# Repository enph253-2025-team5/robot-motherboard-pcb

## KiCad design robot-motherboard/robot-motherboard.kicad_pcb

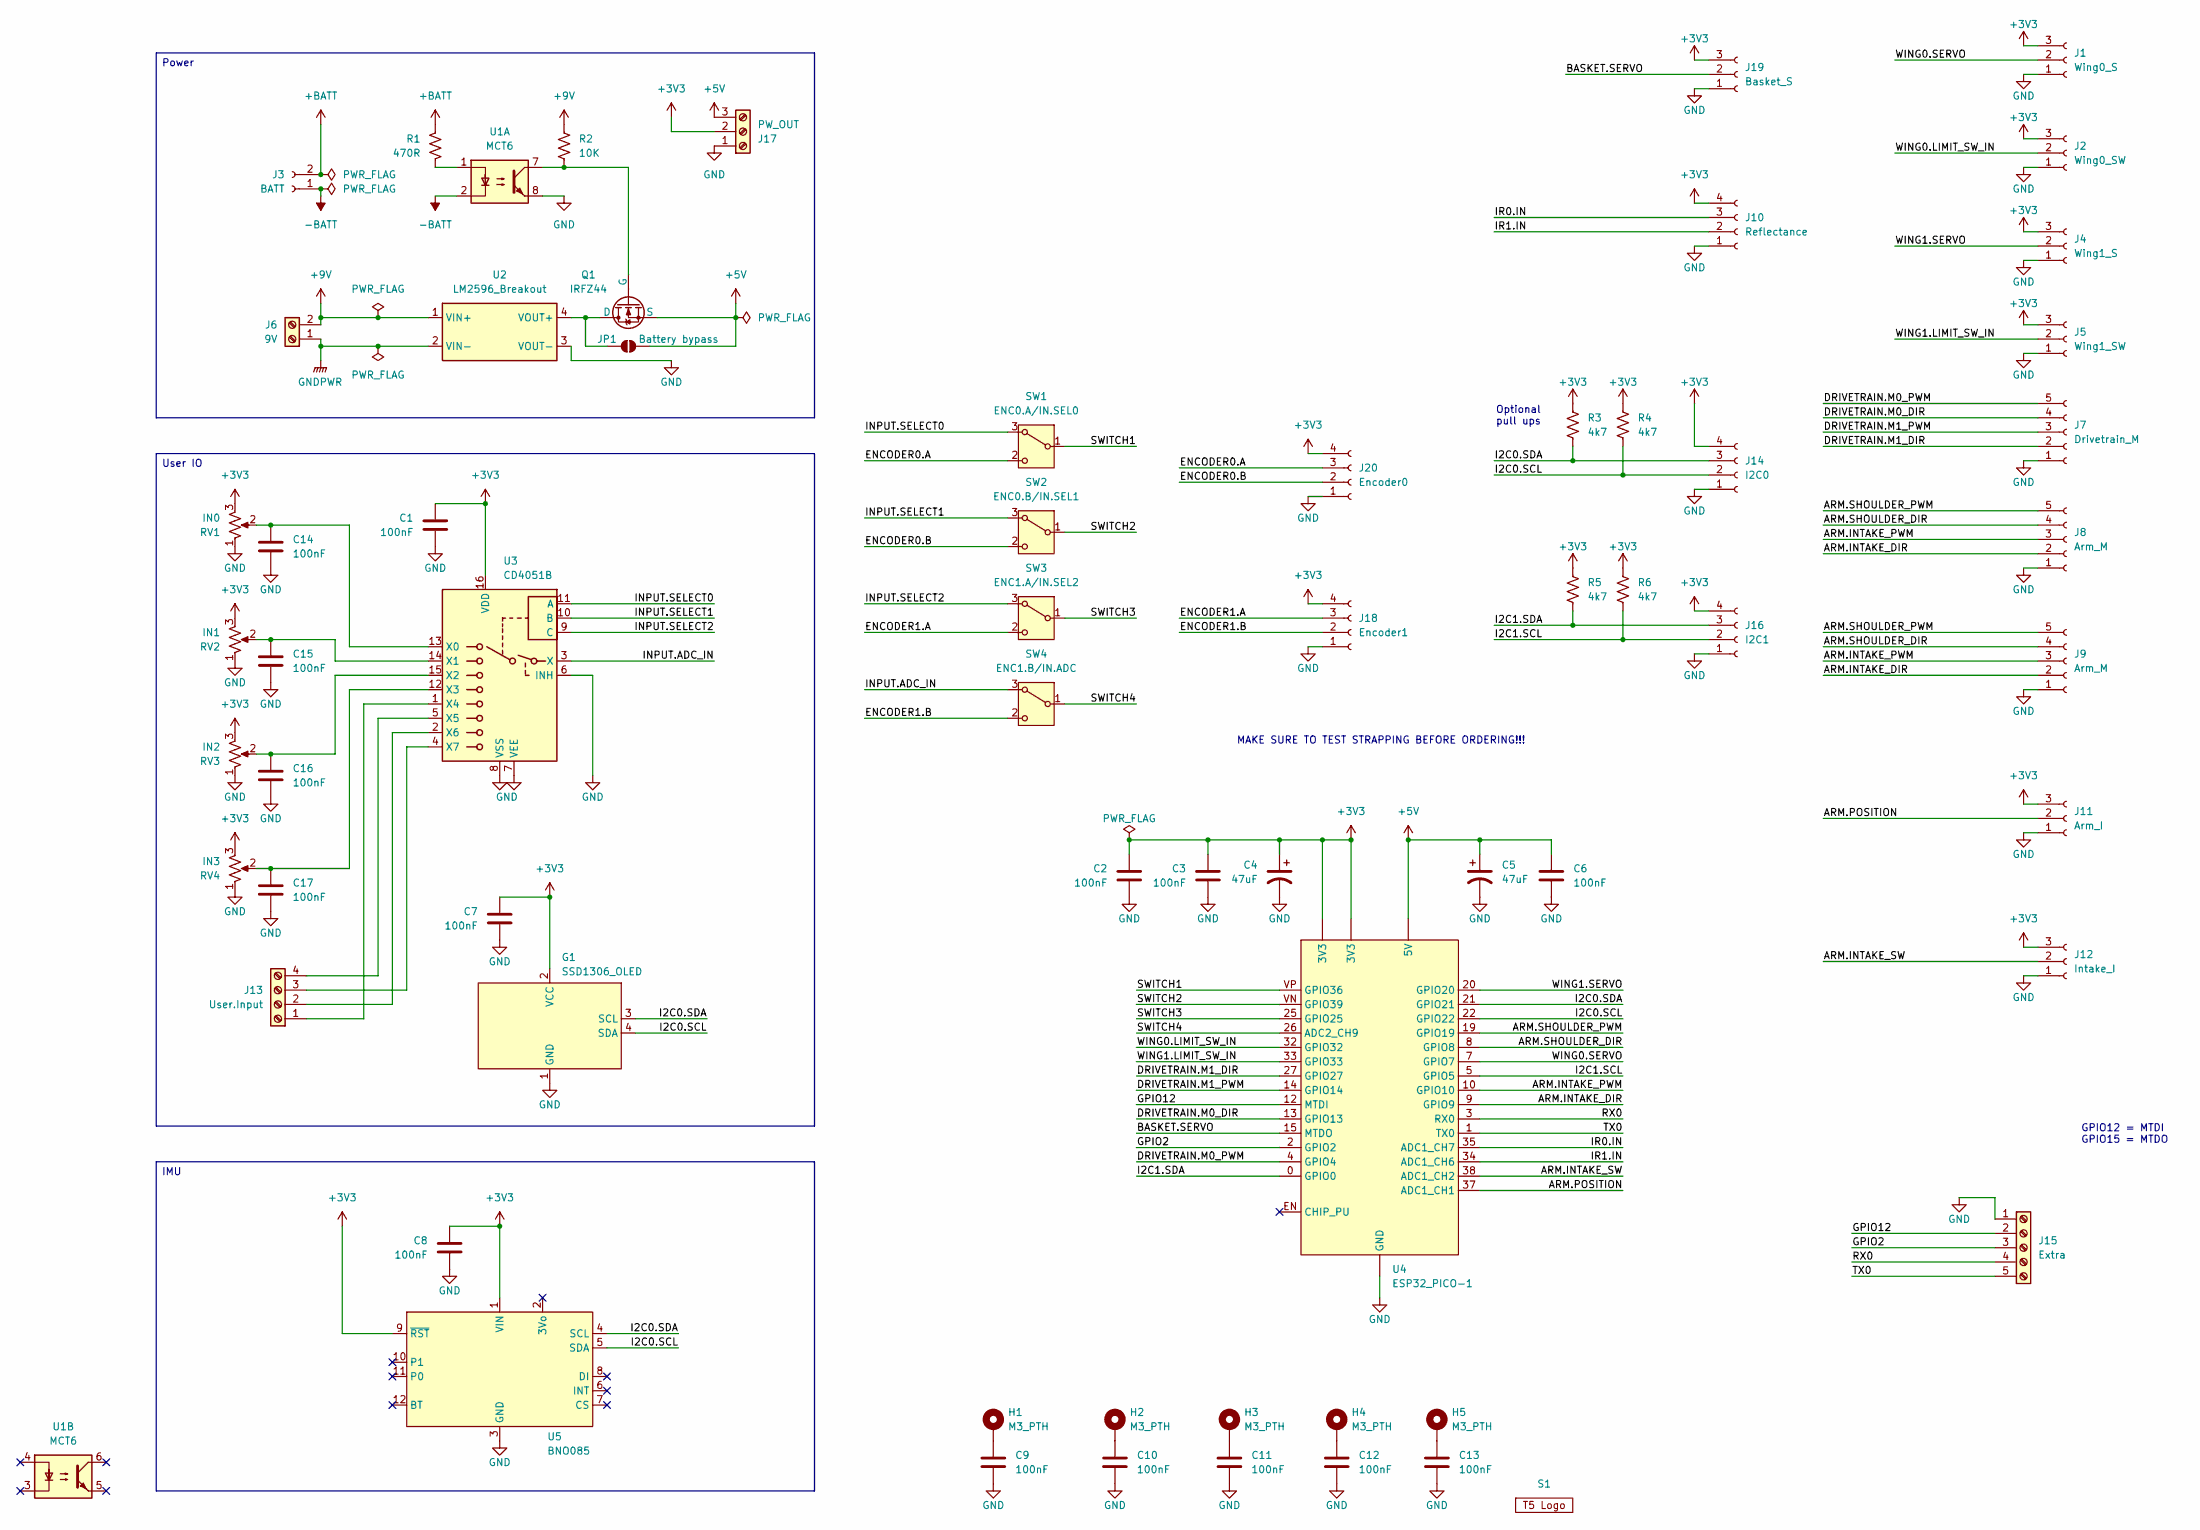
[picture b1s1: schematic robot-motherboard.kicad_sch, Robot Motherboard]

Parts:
C1, C2, C3, C6, C7, C8, C9, C10, C11, C12, C13, C14, C15, C16, C17: 100nF; C_Disc_D3.0mm_W2.0mm_P2.50mm
C4, C5: 47uF; CP_Radial_D5.0mm_P2.00mm
G1: SSD1306_OLED; ADAFRUIT_SSD1306_OLED
H1, H2, H3, H4, H5: M3_PTH; MountingHole_3.2mm_M3_Pad
J1: Wing0_S; JST_XH_S3B-XH-A-1_1x03_P2.50mm_Horizontal
J2: Wing0_SW; JST_XH_S3B-XH-A-1_1x03_P2.50mm_Horizontal
J3: BATT; JST_XH_S2B-XH-A-1_1x02_P2.50mm_Horizontal
J4: Wing1_S; JST_XH_S3B-XH-A-1_1x03_P2.50mm_Horizontal
J5: Wing1_SW; JST_XH_S3B-XH-A-1_1x03_P2.50mm_Horizontal
J6: 9V; TerminalBlock_Xinya_XY308-2.54-2P_1x02_P2.54mm_Horizontal
J7: Drivetrain_M; JST_XH_B5B-XH-A_1x05_P2.50mm_Vertical
J8, J9: Arm_M; JST_XH_B5B-XH-A_1x05_P2.50mm_Vertical
J10: Reflectance; JST_XH_B4B-XH-A_1x04_P2.50mm_Vertical
J11: Arm_I; JST_XH_B3B-XH-A_1x03_P2.50mm_Vertical
J12: Intake_I; JST_XH_B3B-XH-A_1x03_P2.50mm_Vertical
J13: User.Input; TerminalBlock_Xinya_XY308-2.54-4P_1x04_P2.54mm_Horizontal
J14: I2C0; JST_XH_S4B-XH-A-1_1x04_P2.50mm_Horizontal
J15: Extra; TerminalBlock_Xinya_XY308-2.54-5P_1x05_P2.54mm_Horizontal
J16: I2C1; JST_XH_S4B-XH-A-1_1x04_P2.50mm_Horizontal
J17: PW_OUT; TerminalBlock_Xinya_XY308-2.54-3P_1x03_P2.54mm_Horizontal
J18: Encoder1; JST_XH_B4B-XH-A_1x04_P2.50mm_Vertical
J19: Basket_S; JST_XH_B3B-XH-A_1x03_P2.50mm_Vertical
J20: Encoder0; JST_XH_B4B-XH-A_1x04_P2.50mm_Vertical
JP1: Battery bypass; SolderJumper-2_P1.3mm_Open_TrianglePad1.0x1.5mm
Q1: IRFZ44; TO-220-3_Horizontal_TabDown
R1: 470R; R_Axial_DIN0309_L9.0mm_D3.2mm_P12.70mm_Horizontal
R2: 10K; R_Axial_DIN0309_L9.0mm_D3.2mm_P12.70mm_Horizontal
R3, R4, R5, R6: 4k7; R_Axial_DIN0309_L9.0mm_D3.2mm_P12.70mm_Horizontal
RV1: IN0; ENPH253_Potentiometer
RV2: IN1; ENPH253_Potentiometer
RV3: IN2; ENPH253_Potentiometer
RV4: IN3; ENPH253_Potentiometer
S1: Logo; ENPH253_Logo
SW1: ENC0.A/IN.SEL0; SW_Slide-03_Wuerth-WS-SLTV_10x2.5x6.4_P2.54mm
SW2: ENC0.B/IN.SEL1; SW_Slide-03_Wuerth-WS-SLTV_10x2.5x6.4_P2.54mm
SW3: ENC1.A/IN.SEL2; SW_Slide-03_Wuerth-WS-SLTV_10x2.5x6.4_P2.54mm
SW4: ENC1.B/IN.ADC; SW_Slide-03_Wuerth-WS-SLTV_10x2.5x6.4_P2.54mm
U1: MCT6; DIP-8_W7.62mm_LongPads
U2: LM2596_Breakout
U3: CD4051B; DIP-16_W7.62mm_LongPads
U4: ESP32_PICO-1; ESP32_PICO_1_DEV_KIT
U5: BNO085; ADAFRUIT_BNO085

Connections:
+3V3: C1.1, C2.1, C3.1, C4.1, C7.1, C8.1, G1.2 (VCC), J1.3, J2.3, J4.3, J5.3, J10.4, J11.3, J12.3, J14.4, J16.4, J17.2, J18.4, J19.3, J20.4, R3.1, R4.1, R5.1, R6.1, RV1.3, RV2.3, RV3.3, RV4.3, U3.16 (VDD), U4.3V3, U5.1 (VIN), U5.9 (~RST)
+5V: C5.1, C6.1, J17.3, JP1.2 (B), Q1.3 (S), U4.5V
+9V: J6.2, R2.2, U2.1 (VIN+)
+BATT: J3.2, R1.2
-BATT: J3.1, U1.2
/ARM.INTAKE_DIR: J8.2, J9.2, U4.9 (GPIO9)
/ARM.INTAKE_PWM: J8.3, J9.3, U4.10 (GPIO10)
/ARM.INTAKE_SW: J12.2, U4.38 (ADC1_CH2)
/ARM.POSITION: J11.2, U4.37 (ADC1_CH1)
/ARM.SHOULDER_DIR: J8.4, J9.4, U4.8 (GPIO8)
/ARM.SHOULDER_PWM: J8.5, J9.5, U4.19 (GPIO19)
/BASKET.SERVO: J19.2, U4.15 (MTDO)
/DRIVETRAIN.M0_DIR: J7.4, U4.13 (GPIO13)
/DRIVETRAIN.M0_PWM: J7.5, U4.4 (GPIO4)
/DRIVETRAIN.M1_DIR: J7.2, U4.27 (GPIO27)
/DRIVETRAIN.M1_PWM: J7.3, U4.14 (GPIO14)
/ENCODER0.A: J20.3, SW1.2 (C)
/ENCODER0.B: J20.2, SW2.2 (C)
/ENCODER1.A: J18.3, SW3.2 (C)
/ENCODER1.B: J18.2, SW4.2 (C)
/GPIO2: J15.3, U4.2 (GPIO2)
/GPIO12: J15.2, U4.12 (MTDI)
/I2C0.SCL: G1.4 (SDA), J14.2, R4.2, U4.22 (GPIO22), U5.5 (SDA)
/I2C0.SDA: G1.3 (SCL), J14.3, R3.2, U4.21 (GPIO21), U5.4 (SCL)
/I2C1.SCL: J16.2, R6.2, U4.5 (GPIO5)
/I2C1.SDA: J16.3, R5.2, U4.0 (GPIO0)
/INPUT.ADC_IN: SW4.3 (A), U3.3 (X)
/INPUT.SELECT0: SW1.3 (A), U3.11 (A)
/INPUT.SELECT1: SW2.3 (A), U3.10 (B)
/INPUT.SELECT2: SW3.3 (A), U3.9 (C)
/IR0.IN: J10.3, U4.35 (ADC1_CH7)
/IR1.IN: J10.2, U4.34 (ADC1_CH6)
/RX0: J15.4, U4.3 (RX0)
/SWITCH1: SW1.1 (B), U4.VP (GPIO36)
/SWITCH2: SW2.1 (B), U4.VN (GPIO39)
/SWITCH3: SW3.1 (B), U4.25 (GPIO25)
/SWITCH4: SW4.1 (B), U4.26 (ADC2_CH9)
/TX0: J15.5, U4.1 (TX0)
/WING0.LIMIT_SW_IN: J2.2, U4.32 (GPIO32)
/WING0.SERVO: J1.2, U4.7 (GPIO7)
/WING1.LIMIT_SW_IN: J5.2, U4.33 (GPIO33)
/WING1.SERVO: J4.2, U4.20 (GPIO20)
GND: C1.2, C2.2, C3.2, C4.2, C5.2, C6.2, C7.2, C8.2, C9.2, C10.2, C11.2, C12.2, C13.2, C14.2, C15.2, C16.2, C17.2, G1.1 (GND), J1.1, J2.1, J4.1, J5.1, J7.1, J8.1, J9.1, J10.1, J11.1, J12.1, J14.1, J15.1, J16.1, J17.1, J18.1, J19.1, J20.1, RV1.1, RV2.1, RV3.1, RV4.1, U1.8, U2.3 (VOUT-), U3.6 (INH), U3.7 (VEE), U3.8 (VSS), U4.GND, U5.3 (GND)
GNDPWR: J6.1, U2.2 (VIN-)
unnamed: C9.1, H1.1
unnamed: C10.1, H2.1
unnamed: C11.1, H3.1
unnamed: C12.1, H4.1
unnamed: C13.1, H5.1
unnamed: J13.1, U3.1 (X4)
unnamed: J13.2, U3.2 (X6)
unnamed: J13.3, U3.4 (X7)
unnamed: J13.4, U3.5 (X5)
unnamed: JP1.1 (A), Q1.2 (D), U2.4 (VOUT+)
unnamed: Q1.1 (G), R2.1, U1.7
unnamed: R1.1, U1.1
unnamed: C14.1, RV1.2, U3.13 (X0)
unnamed: C15.1, RV2.2, U3.14 (X1)
unnamed: C16.1, RV3.2, U3.15 (X2)
unnamed: C17.1, RV4.2, U3.12 (X3)

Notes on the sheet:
Optional pull ups
GPIO12 = MTDI GPIO15 = MTDO
MAKE SURE TO TEST STRAPPING BEFORE ORDERING!!!
User IO
Power
IMU

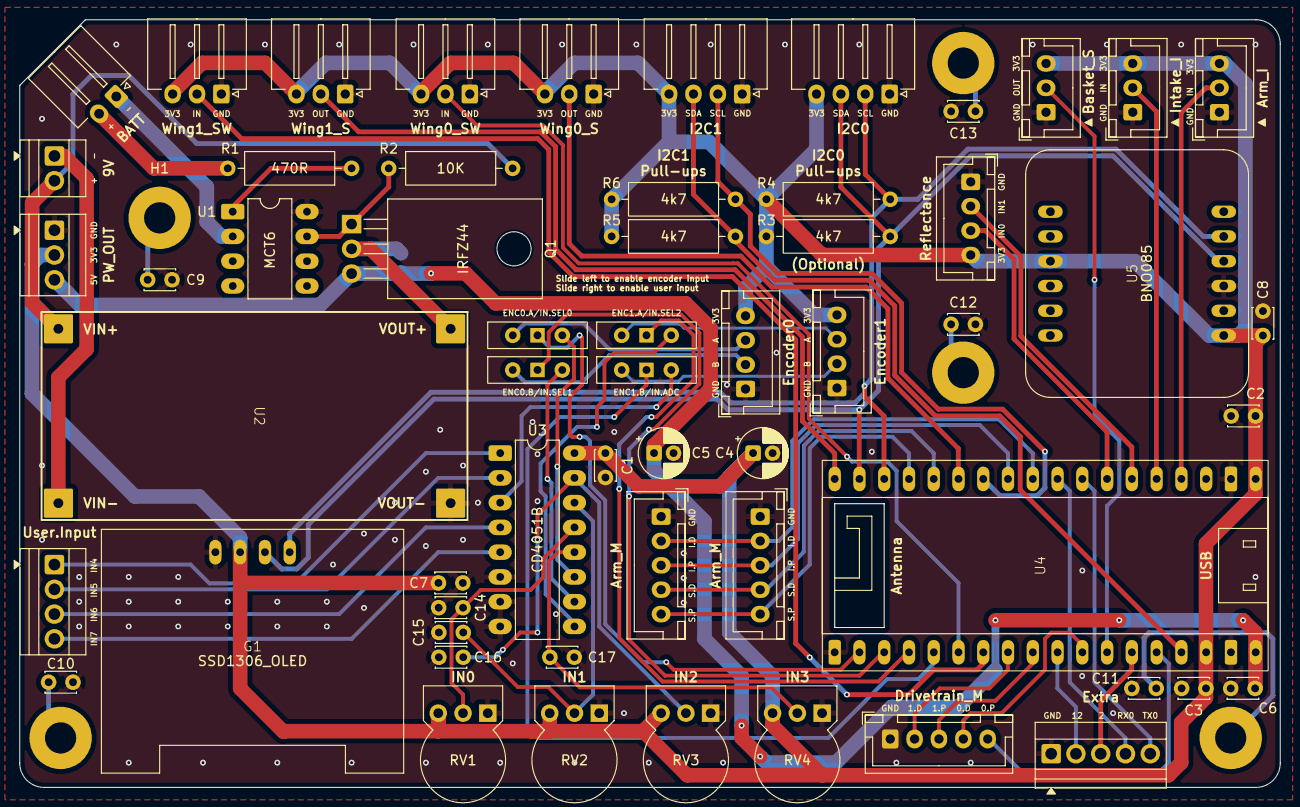
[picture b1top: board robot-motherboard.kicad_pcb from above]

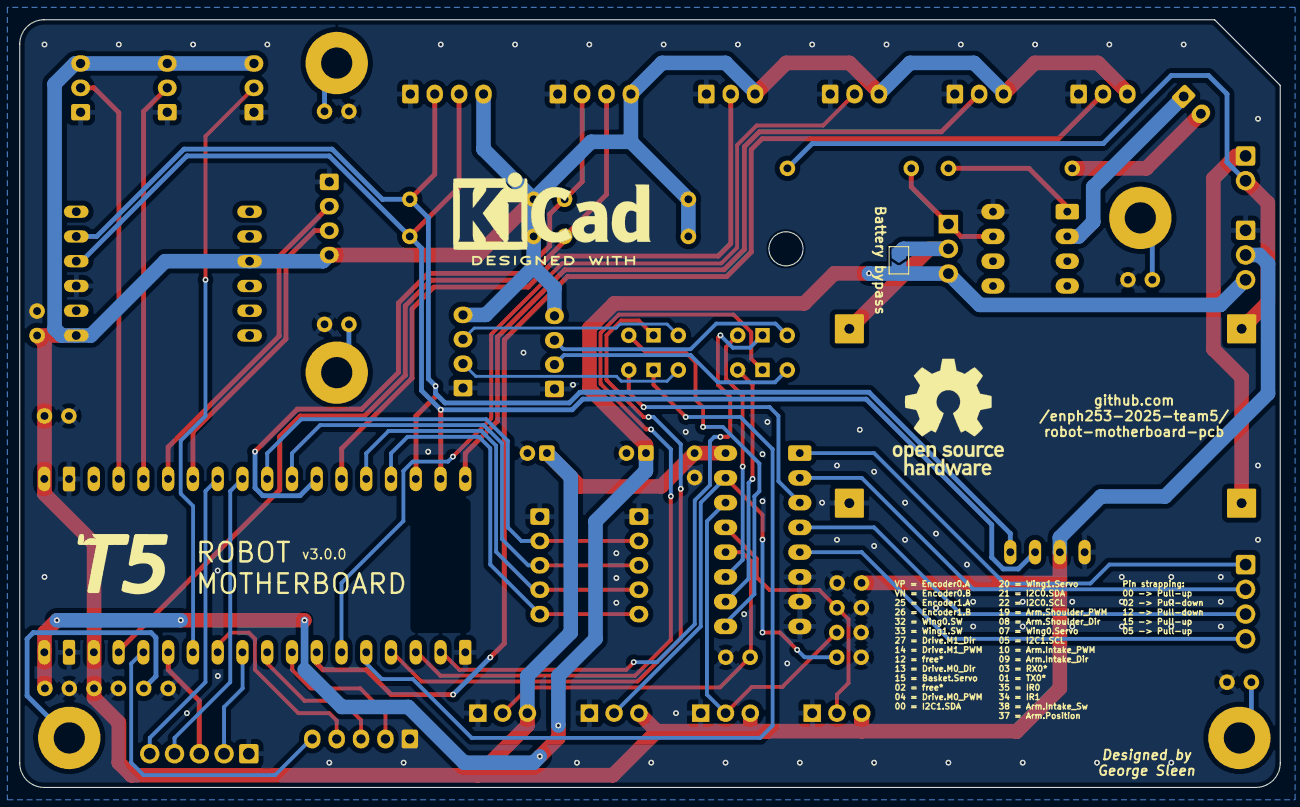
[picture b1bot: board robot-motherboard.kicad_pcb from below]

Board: 2 copper layers, 129.3 x 78.7 mm, 65 parts (2 on the bottom side), 60 nets.

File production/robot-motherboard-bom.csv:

"Value","Qty","Reference","Footprint"
"SSD1306_OLED","1","G1","GS_Development_Boards:ADAFRUIT_SSD1306_OLED"
"BNO085","1","U5","GS_Development_Boards:ADAFRUIT_BNO085"
"LM2596_Breakout","1","U2","GS_Development_Boards:LM2596_Breakout"
"CD4051B","1","U3","Package_DIP:DIP-16_W7.62mm_LongPads"
"MCT6","1","U1","Package_DIP:DIP-8_W7.62mm_LongPads"
"ESP32_PICO-1","1","U4","GS_Development_Boards:ESP32_PICO_1_DEV_KIT"
"BATT","1","J3","GS_Connectors:JST_XH_S2B-XH-A-1_1x02_P2.50mm_Horizontal"
"Wing0_S","1","J1","GS_Connectors:JST_XH_S3B-XH-A-1_1x03_P2.50mm_Horizontal"
"Wing0_SW","1","J2","GS_Connectors:JST_XH_S3B-XH-A-1_1x03_P2.50mm_Horizontal"
"Wing1_S","1","J4","GS_Connectors:JST_XH_S3B-XH-A-1_1x03_P2.50mm_Horizontal"
"Wing1_SW","1","J5","GS_Connectors:JST_XH_S3B-XH-A-1_1x03_P2.50mm_Horizontal"
"Arm_I","1","J11","Connector_JST:JST_XH_B3B-XH-A_1x03_P2.50mm_Vertical"
"Intake_I","1","J12","Connector_JST:JST_XH_B3B-XH-A_1x03_P2.50mm_Vertical"
"Basket_S","1","J19","Connector_JST:JST_XH_B3B-XH-A_1x03_P2.50mm_Vertical"
"Reflectance","1","J10","Connector_JST:JST_XH_B4B-XH-A_1x04_P2.50mm_Vertical"
"I2C0","1","J14","GS_Connectors:JST_XH_S4B-XH-A-1_1x04_P2.50mm_Horizontal"
"I2C1","1","J16","GS_Connectors:JST_XH_S4B-XH-A-1_1x04_P2.50mm_Horizontal"
"Encoder1","1","J18","Connector_JST:JST_XH_B4B-XH-A_1x04_P2.50mm_Vertical"
"Encoder0","1","J20","Connector_JST:JST_XH_B4B-XH-A_1x04_P2.50mm_Vertical"
"Drivetrain_M","1","J7","Connector_JST:JST_XH_B5B-XH-A_1x05_P2.50mm_Vertical"
"Arm_M","2","J8,J9","Connector_JST:JST_XH_B5B-XH-A_1x05_P2.50mm_Vertical"
"9V","1","J6","TerminalBlock:TerminalBlock_Xinya_XY308-2.54-2P_1x02_P2.54mm_Horizontal"
"PW_OUT","1","J17","TerminalBlock:TerminalBlock_Xinya_XY308-2.54-3P_1x03_P2.54mm_Horizontal"
"User.Input","1","J13","TerminalBlock:TerminalBlock_Xinya_XY308-2.54-4P_1x04_P2.54mm_Horizontal"
"Extra","1","J15","TerminalBlock:TerminalBlock_Xinya_XY308-2.54-5P_1x05_P2.54mm_Horizontal"
"IRFZ44","1","Q1","Package_TO_SOT_THT:TO-220-3_Horizontal_TabDown"
"47uF","2","C4,C5","Capacitor_THT:CP_Radial_D5.0mm_P2.00mm"
"IN0","1","RV1","GS_Resistors:ENPH253_Potentiometer"
"IN1","1","RV2","GS_Resistors:ENPH253_Potentiometer"
"IN2","1","RV3","GS_Resistors:ENPH253_Potentiometer"
"IN3","1","RV4","GS_Resistors:ENPH253_Potentiometer"
"470R","1","R1","Resistor_THT:R_Axial_DIN0309_L9.0mm_D3.2mm_P12.70mm_Horizontal"
"10K","1","R2","Resistor_THT:R_Axial_DIN0309_L9.0mm_D3.2mm_P12.70mm_Horizontal"
"4k7","4","R3,R4,R5,R6","Resistor_THT:R_Axial_DIN0309_L9.0mm_D3.2mm_P12.70mm_Horizontal"
"ENC0.A/IN.SEL0","1","SW1","Button_Switch_THT:SW_Slide-03_Wuerth-WS-SLTV_10x2.5x6.4_P2.54mm"
"ENC0.B/IN.SEL1","1","SW2","Button_Switch_THT:SW_Slide-03_Wuerth-WS-SLTV_10x2.5x6.4_P2.54mm"
"ENC1.A/IN.SEL2","1","SW3","Button_Switch_THT:SW_Slide-03_Wuerth-WS-SLTV_10x2.5x6.4_P2.54mm"
"ENC1.B/IN.ADC","1","SW4","Button_Switch_THT:SW_Slide-03_Wuerth-WS-SLTV_10x2.5x6.4_P2.54mm"
"100nF","15","C1,C2,C3,C6,C7,C8,C9,C10,C11,C12,C13,C14,C15,C16,C17","Capacitor_THT:C_Disc_D3.0mm_W2.0mm_P2.50mm"

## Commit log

2025-06-25 Start tracking production outputs
2025-06-25 Initialize KiCad project
2025-07-03 Finish layout
2025-07-04 Generate production files
2025-07-06 Add filtering on user input
2025-07-06 Update back silkscreen
2025-07-06 Update board outline for better access to power jumper
2025-07-07 Add switches between user input and encoder inputs
2025-07-07 Generate production outputs
2025-07-08 Update to the right ESP32 footprint
2025-07-08 Fix production outputs
